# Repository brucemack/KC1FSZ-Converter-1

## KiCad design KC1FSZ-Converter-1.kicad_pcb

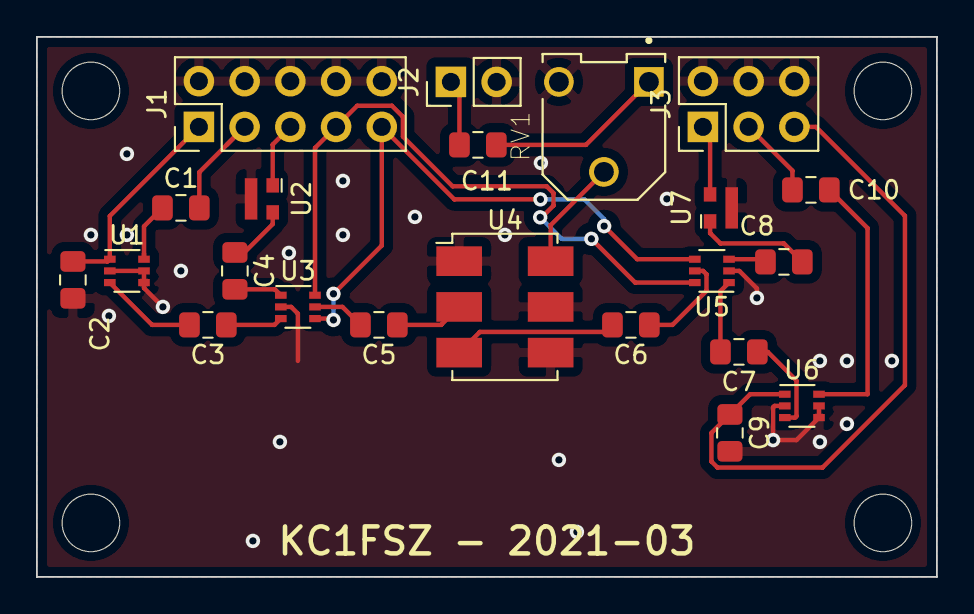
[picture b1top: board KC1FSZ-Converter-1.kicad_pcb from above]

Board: 2 copper layers, 50.0 x 30.0 mm, 26 parts (0 on the bottom side), 26 nets.

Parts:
C1, C2, C3, C4, C5, C6, C7, C8, C9, C10, C11: 0.1U; C_0805_2012Metric_Pad1.15x1.40mm_HandSolder
H1, H2, H3, H4: MountingHole; MountingHole_3.2mm_M3_ISO14580
J1: Conn_02x05_Odd_Even; PinHeader_2x05_P2.54mm_Vertical
J2: Conn_01x02; PinHeader_1x02_P2.54mm_Vertical
J3: Conn_02x03_Odd_Even; PinHeader_2x03_P2.54mm_Vertical
RV1: R_POT; TRIM_3306F-1-101
U1, U6: BGA2867; SOT-363_SC-70-6
U2, U7: PAT1220-C-6DB; RF_Attenuator_Susumu_PAT1220
U3, U5: MASW-007221; SOT-363_SC-70-6
U4: ADE-1+; Mini-Circuits_CD636_H4.11mm

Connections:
+5VA: C2.1, J1.1, U1.1
+5VD: C9.1, J3.5, U6.1
GNDA: C2.2, C9.2, J1.2, J1.4, J1.6, J1.8, J1.10, J2.2, J3.2, J3.4, J3.6, RV1.3, U1.2, U1.4, U1.5, U2.3, U3.2, U4.1, U4.4, U4.5, U5.2, U6.2, U6.4, U6.5, U7.3
LO_IN: C11.1, J2.1
unnamed: C1.1, U1.6
unnamed: C3.1, U3.3
unnamed: C3.2, U1.3
unnamed: C4.1, U2.2
unnamed: C4.2, U3.1
unnamed: C5.1, U4.2
unnamed: C5.2, U3.5
unnamed: C6.1, U5.5
unnamed: C6.2, U4.3
unnamed: C7.1, U6.3
unnamed: C7.2, U5.1
unnamed: C8.1, U7.1
unnamed: C8.2, U5.3
unnamed: C10.2, U6.6
unnamed: C11.2, RV1.1
unnamed: RV1.2, U4.6
RX_IN: C10.1, J3.3
RX_OUT: J1.5, U2.1
SEL1: J1.7, U3.6, U5.6
SEL2: J1.9, U3.4, U5.4
TX_IN: C1.2, J1.3
TX_OUT: J3.1, U7.2

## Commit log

2021-03-24 Working
2021-03-24 Ready for RIT
